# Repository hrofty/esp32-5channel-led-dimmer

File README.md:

# esp32-5channel-led-dimmer
Simple 5 channel dimmer made for R/G/B/CW/WW led strip with optional RTC module.
PCB designed in KiCad 6 and firmware written using Arduino.

wip

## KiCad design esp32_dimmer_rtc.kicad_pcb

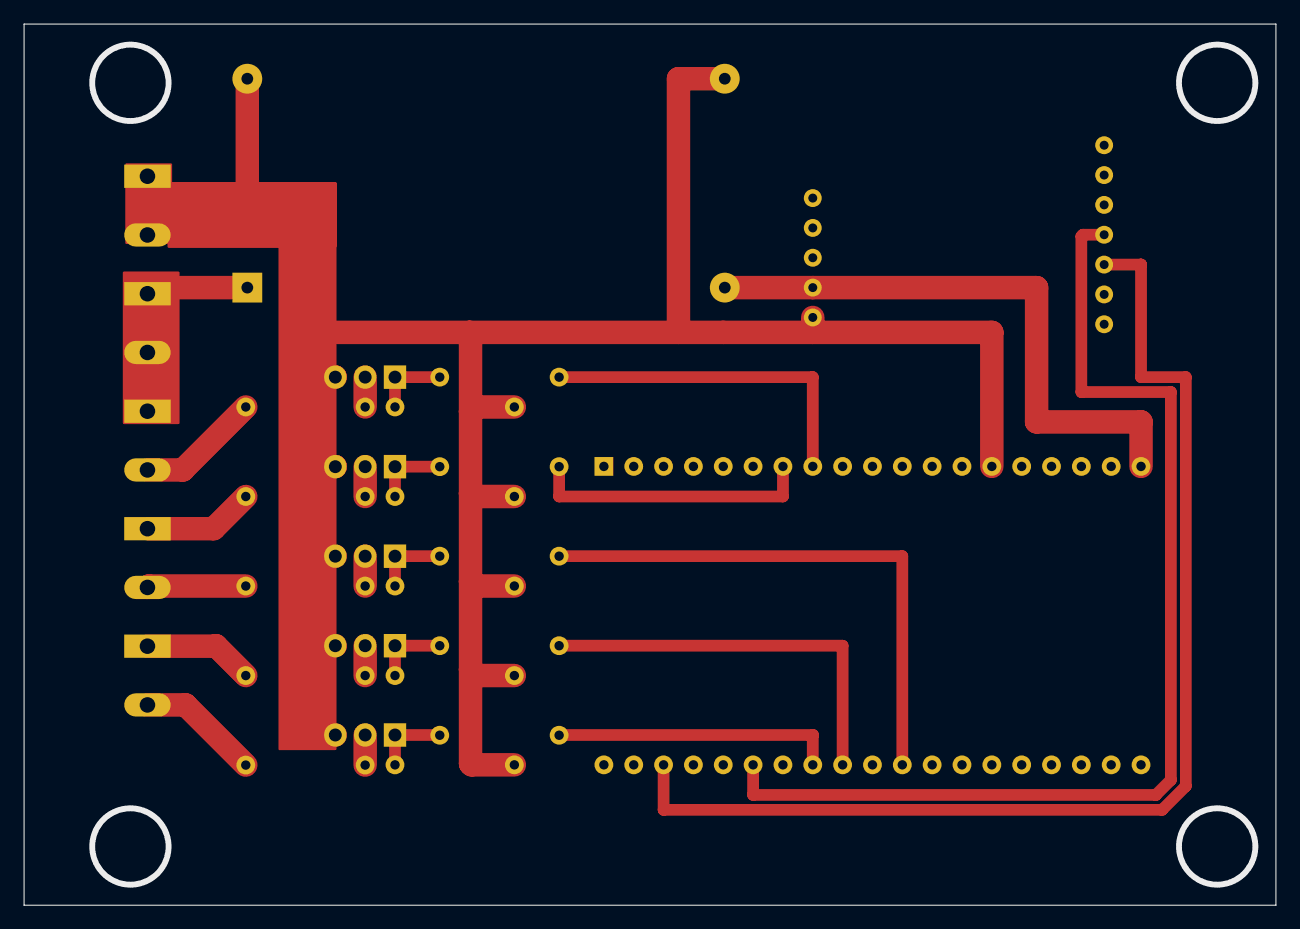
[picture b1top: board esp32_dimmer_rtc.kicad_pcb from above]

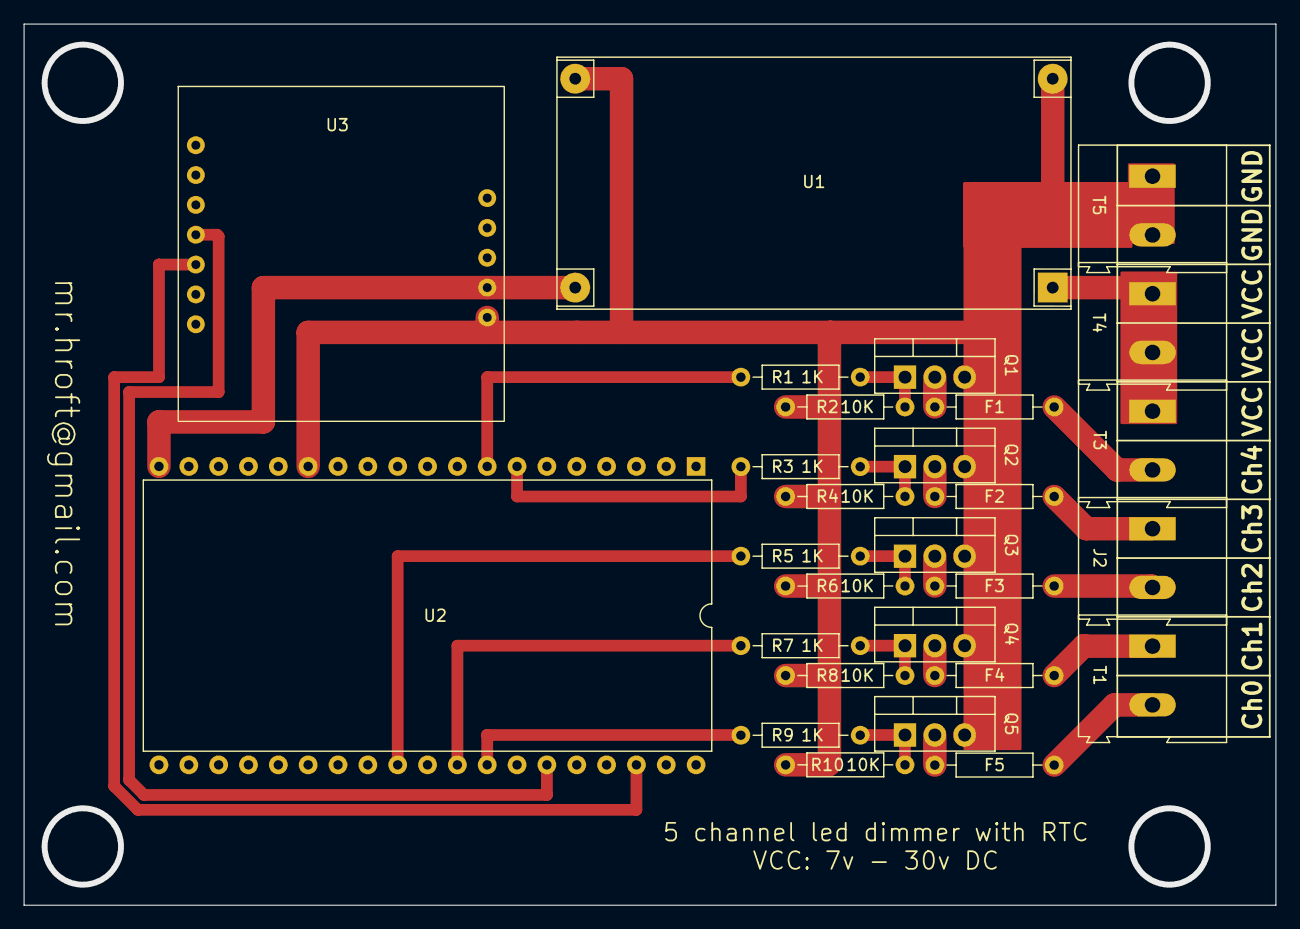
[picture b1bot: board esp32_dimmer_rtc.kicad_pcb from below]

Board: 2 copper layers, 106.6 x 75.0 mm, 28 parts (28 on the bottom side), 25 nets.

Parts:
F1, F2, F3, F4, F5: Polyfuse; fuse
J2: Screw_Terminal_01x02; TerminalBlock_Altech_AK300-2_P5.00mm
Q1, Q2, Q3, Q4, Q5: IRLZ44N; TO-220-3_Vertical
R1, R3, R5, R7, R9: 1K; Resistor_TH_5.08mm_value
R2, R4, R6, R8, R10: 10K; Resistor_TH_5.08mm_value
T1, T3, T4, T5: Screw_Terminal_01x02; TerminalBlock_Altech_AK300-2_P5.00mm
U1: YAAJ_DCDC_StepDown_LM2596; LM2596_DCDC_StepDown
U2: AI-Thinker Nodemcu-32S; ai-thinker nodemcu-32s
U3: Tiny_RTC_DS1307; Tiny_RTC

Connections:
+5V: U1.4 (Vout), U2.19 (5V), U3.9 (VCC)
/channel0/ChannelDrain: F1.1, T3.2
/channel1/ChannelDrain: F2.1, J2.1
/channel2/ChannelDrain: F3.1, J2.2
/channel3/ChannelDrain: F4.1, T1.1
/channel4/ChannelDrain: F5.1, T1.2
Ch0_PWM: R1.1, U2.8 (GPIO33)
Ch1_PWM: R3.1, U2.7 (GPIO32)
Ch2_PWM: R5.1, U2.28 (GPIO17)
Ch3_PWM: R7.1, U2.30 (GPIO18)
Ch4_PWM: R9.1, U2.31 (GPIO19)
GND: Q1.3 (S), Q2.3 (S), Q3.3 (S), Q4.3 (S), Q5.3 (S), R2.1, R4.1, R6.1, R8.1, R10.1, T5.1, T5.2, U1.2 (GND), U1.3 (GND), U2.14 (GND), U3.8 (GND)
unnamed: F1.2, Q1.2 (D)
unnamed: F2.2, Q2.2 (D)
unnamed: F3.2, Q3.2 (D)
unnamed: F4.2, Q4.2 (D)
unnamed: F5.2, Q5.2 (D)
unnamed: Q1.1 (G), R1.2, R2.2
unnamed: Q2.1 (G), R3.2, R4.2
unnamed: Q3.1 (G), R5.2, R6.2
unnamed: Q4.1 (G), R7.2, R8.2
unnamed: Q5.1 (G), R9.2, R10.2
unnamed: U2.33 (GPIO21), U3.4 (SDA)
unnamed: U2.36 (GPIO22), U3.5 (SCL)
VCC: T3.1, T4.1, T4.2, U1.1 (Vin)

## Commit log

2022-05-03 Main Upload
2022-05-12 Restructred folders a bit
2022-05-12 some readme additions
2022-05-12 added placeholder firmware for testing
2022-05-15 minor time adjustments in placeholder
2022-05-16 Big placeholder rework
2022-05-16 webserver beginings
2022-05-16 Webserver work
2022-05-16 added save and load to timeline
    need to fix heap corruption thou
2022-05-17 fixed crushes and cleaned up a bit
2022-05-18 added superspeed and dumper options
